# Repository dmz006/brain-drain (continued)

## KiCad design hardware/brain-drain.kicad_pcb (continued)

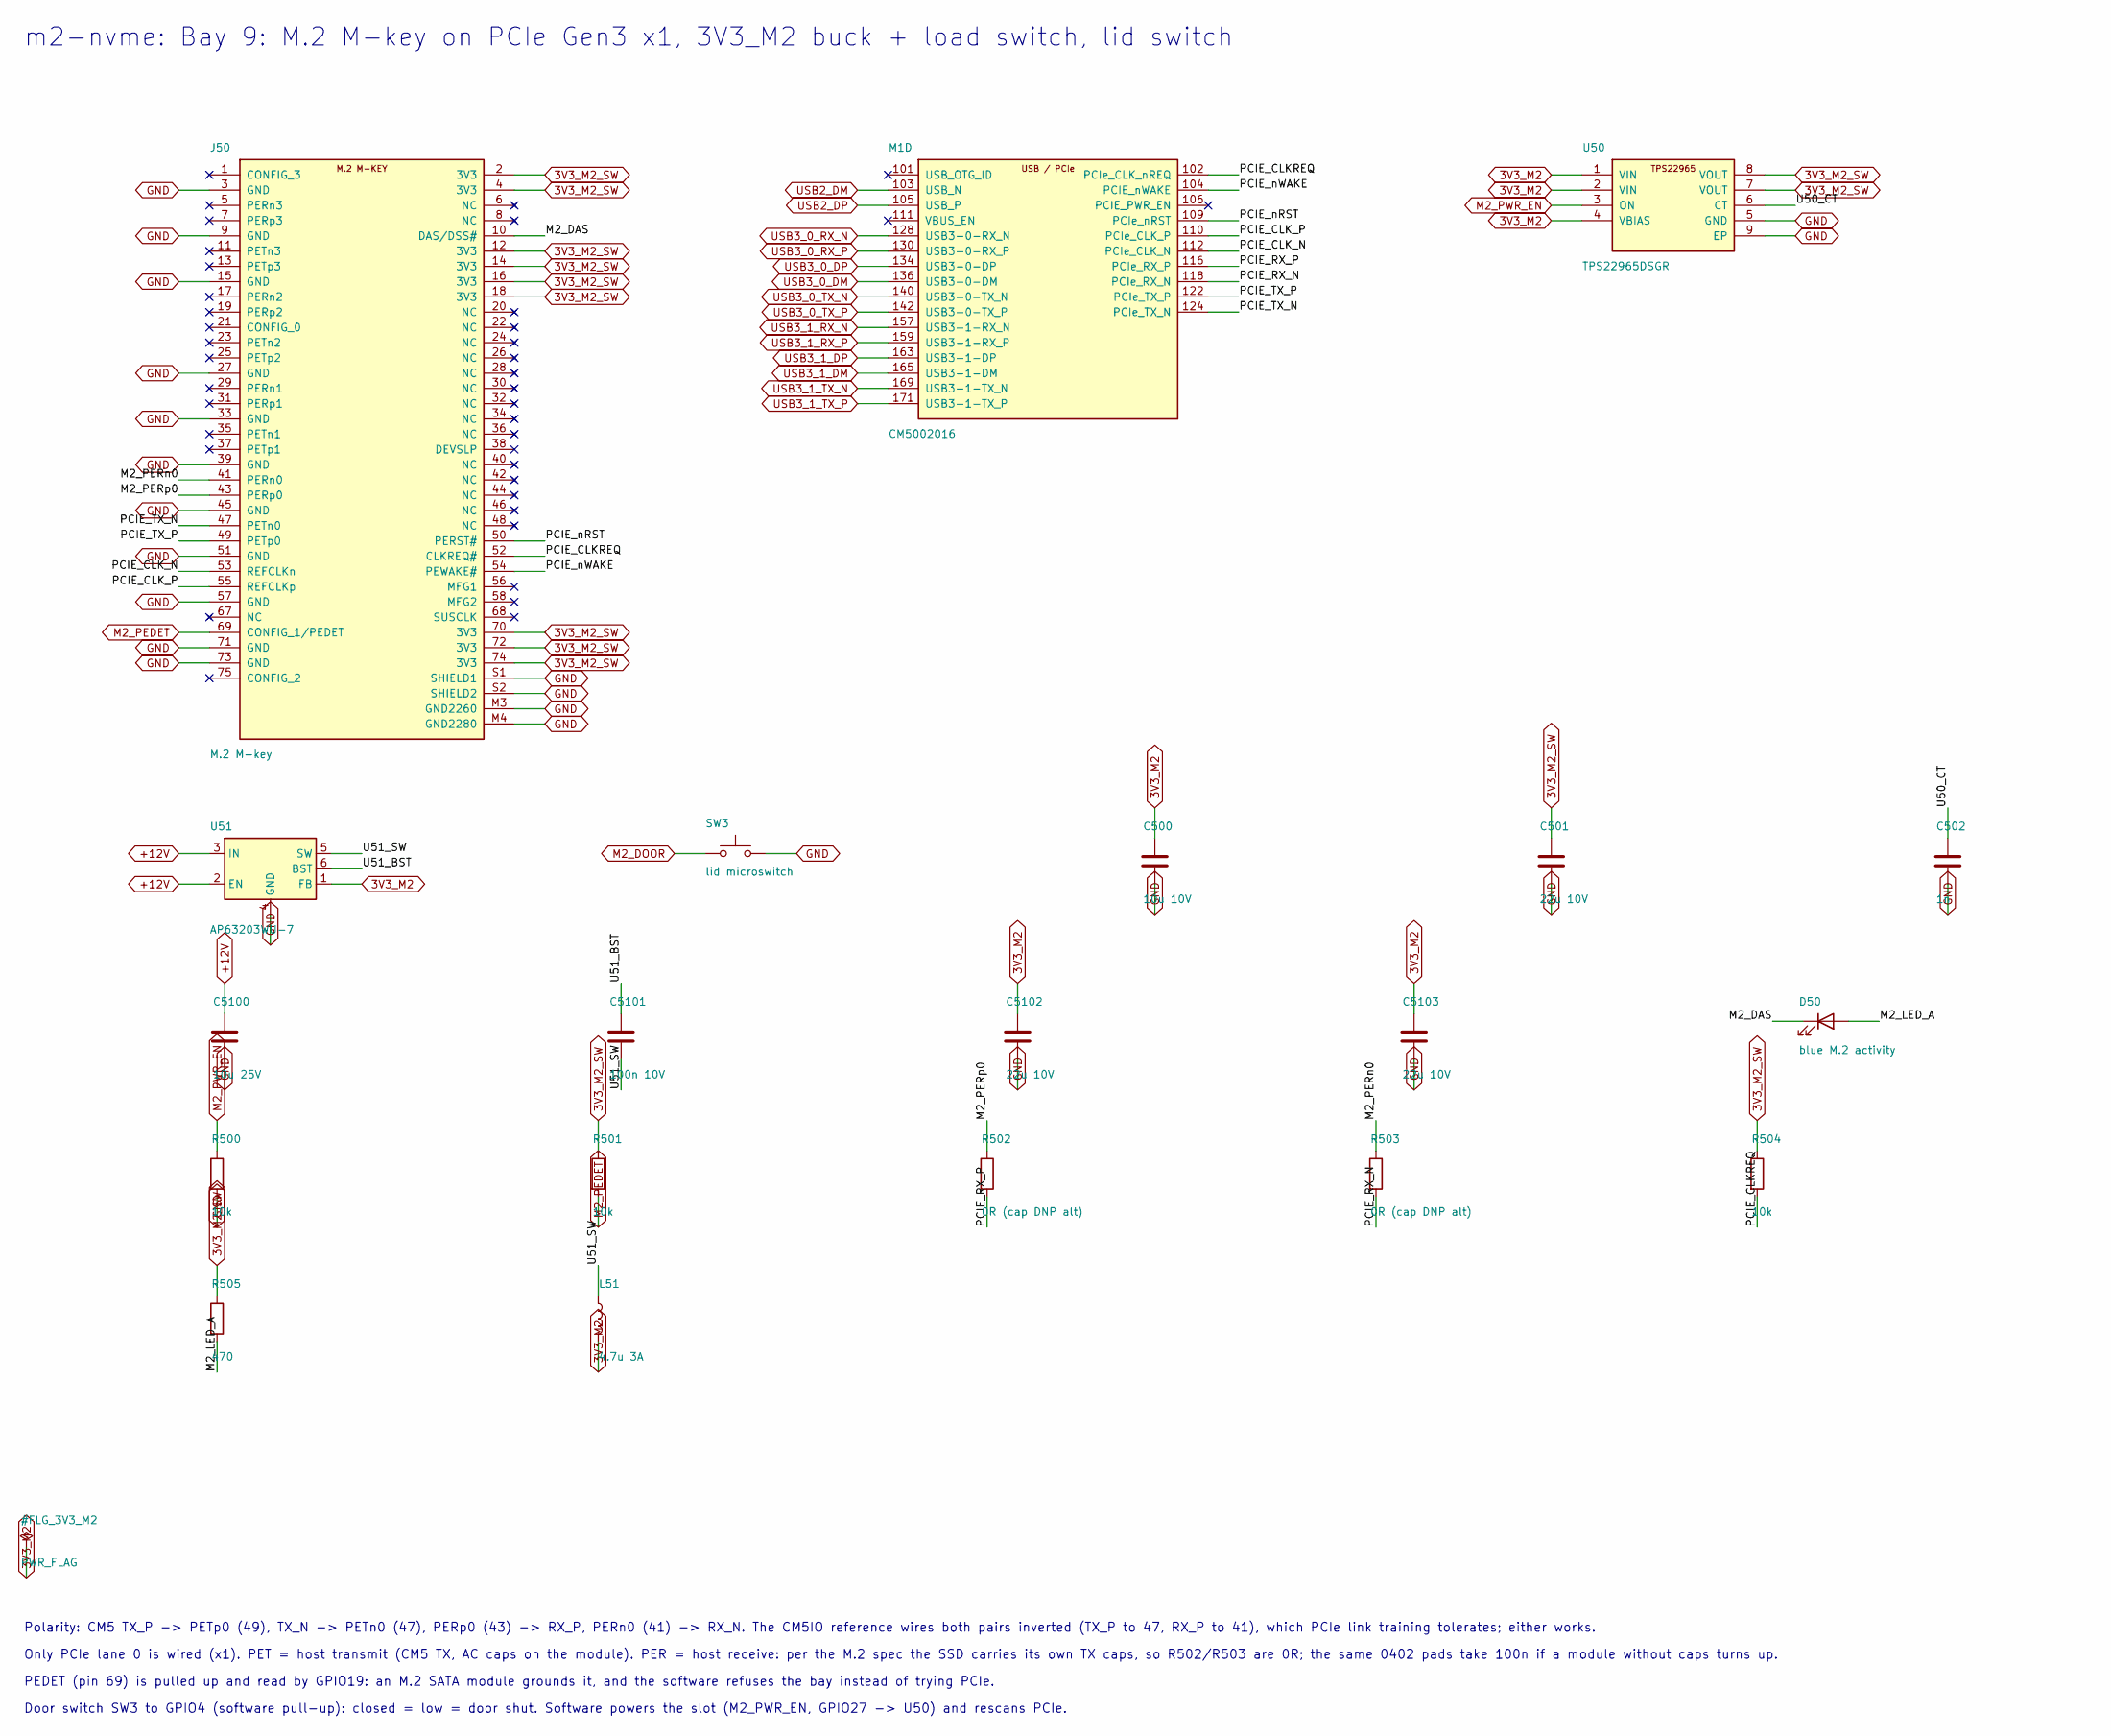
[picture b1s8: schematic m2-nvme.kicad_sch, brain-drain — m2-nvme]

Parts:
C500: 10u 10V; C_0805_2012Metric
C501, C5102, C5103: 22u 10V; C_0805_2012Metric
C502: 1n; C_0402_1005Metric
C5100: 10u 25V; C_1210_3225Metric
C5101: 100n 10V; C_0402_1005Metric
D50: blue M.2 activity; LED_D3.0mm
J50: M.2 M-key; M2_Socket3_MKey_CM5IO
L51: 4.7u 3A; L_Taiyo-Yuden_NR-40xx
M1: CM5002016; Raspberry-Pi-5-Compute-Module
R500, R501, R504: 10k; R_0402_1005Metric
R502, R503: 0R (cap DNP alt); C_0402_1005Metric
R505: 470; R_0402_1005Metric
SW3: lid microswitch; SW_PUSH_6mm
U50: TPS22965DSGR; Texas_DSG0008A_WSON-8-1EP_2x2mm_P0.5mm_EP0.9x1.6mm
U51: AP63203WU-7; TSOT-23-6

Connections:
3V3_M2: C500.1, C5102.1, C5103.1, L51.2, U50.1 (VIN), U50.2 (VIN), U50.4 (VBIAS), U51.1 (FB)
3V3_M2_SW: C501.1, J50.2 (3V3), J50.4 (3V3), J50.12 (3V3), J50.14 (3V3), J50.16 (3V3), J50.18 (3V3), J50.70 (3V3), J50.72 (3V3), J50.74 (3V3), R501.1, R504.1, R505.1, U50.7 (VOUT), U50.8 (VOUT)
+12V: C5100.1, U51.2 (EN), U51.3 (IN); also elsewhere on the board
GND: C500.2, C501.2, C502.2, C5100.2, C5102.2, C5103.2, J50.3 (GND), J50.9 (GND), J50.15 (GND), J50.27 (GND), J50.33 (GND), J50.39 (GND), J50.45 (GND), J50.51 (GND), J50.57 (GND), J50.71 (GND), J50.73 (GND), J50.M3 (GND2260), J50.M4 (GND2280), J50.S1 (SHIELD1), J50.S2 (SHIELD2), R500.2, SW3.2, U50.5 (GND), U50.9 (EP), U51.4 (GND); also elsewhere on the board
M2_DAS: D50.1 (K), J50.10 (DAS/DSS#)
M2_DOOR: SW3.1; also elsewhere on the board
M2_LED_A: D50.2 (A), R505.2
M2_PEDET: J50.69 (CONFIG_1/PEDET), R501.2; also elsewhere on the board
M2_PERn0: J50.41 (PERn0), R503.1
M2_PERp0: J50.43 (PERp0), R502.1
M2_PWR_EN: R500.1, U50.3 (ON); also elsewhere on the board
PCIE_CLKREQ: J50.52 (CLKREQ#), M1.102 (PCIe_CLK_nREQ), R504.2
PCIE_CLK_N: J50.53 (REFCLKn), M1.112 (PCIe_CLK_N)
PCIE_CLK_P: J50.55 (REFCLKp), M1.110 (PCIe_CLK_P)
PCIE_RX_N: M1.118 (PCIe_RX_N), R503.2
PCIE_RX_P: M1.116 (PCIe_RX_P), R502.2
PCIE_TX_N: J50.47 (PETn0), M1.124 (PCIe_TX_N)
PCIE_TX_P: J50.49 (PETp0), M1.122 (PCIe_TX_P)
PCIE_nRST: J50.50 (PERST#), M1.109 (PCIe_nRST)
PCIE_nWAKE: J50.54 (PEWAKE#), M1.104 (PCIE_nWAKE)
U50_CT: C502.1, U50.6 (CT)
U51_BST: C5101.1, U51.6 (BST)
U51_SW: C5101.2, L51.1, U51.5 (SW)
USB2_DM: M1.103 (USB_N); also elsewhere on the board
USB2_DP: M1.105 (USB_P); also elsewhere on the board
USB3_0_DM: M1.136 (USB3-0-DM); also elsewhere on the board
USB3_0_DP: M1.134 (USB3-0-DP); also elsewhere on the board
USB3_0_RX_N: M1.128 (USB3-0-RX_N); also elsewhere on the board
USB3_0_RX_P: M1.130 (USB3-0-RX_P); also elsewhere on the board
USB3_0_TX_N: M1.140 (USB3-0-TX_N); also elsewhere on the board
USB3_0_TX_P: M1.142 (USB3-0-TX_P); also elsewhere on the board
USB3_1_DM: M1.165 (USB3-1-DM); also elsewhere on the board
USB3_1_DP: M1.163 (USB3-1-DP); also elsewhere on the board
USB3_1_RX_N: M1.157 (USB3-1-RX_N); also elsewhere on the board
USB3_1_RX_P: M1.159 (USB3-1-RX_P); also elsewhere on the board
USB3_1_TX_N: M1.169 (USB3-1-TX_N); also elsewhere on the board
USB3_1_TX_P: M1.171 (USB3-1-TX_P); also elsewhere on the board

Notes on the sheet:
m2-nvme: Bay 9: M.2 M-key on PCIe Gen3 x1, 3V3_M2 buck + load switch, lid switch
Polarity: CM5 TX_P -> PETp0 (49), TX_N -> PETn0 (47), PERp0 (43) -> RX_P, PERn0 (41) -> RX_N. The CM5IO reference wires both pairs inverted (TX_P to 47, RX_P to 41), which PCIe link training tolerates; either works.
Only PCIe lane 0 is wired (x1). PET = host transmit (CM5 TX, AC caps on the module). PER = host receive: per the M.2 spec the SSD carries its own TX caps, so R502/R503 are 0R; the same 0402 pads take 100n if a module without caps turns up.
PEDET (pin 69) is pulled up and read by GPIO19: an M.2 SATA module grounds it, and the software refuses the bay instead of trying PCIe.
Door switch SW3 to GPIO4 (software pull-up): closed = low = door shut. Software powers the slot (M2_PWR_EN, GPIO27 -> U50) and rescans PCIe.

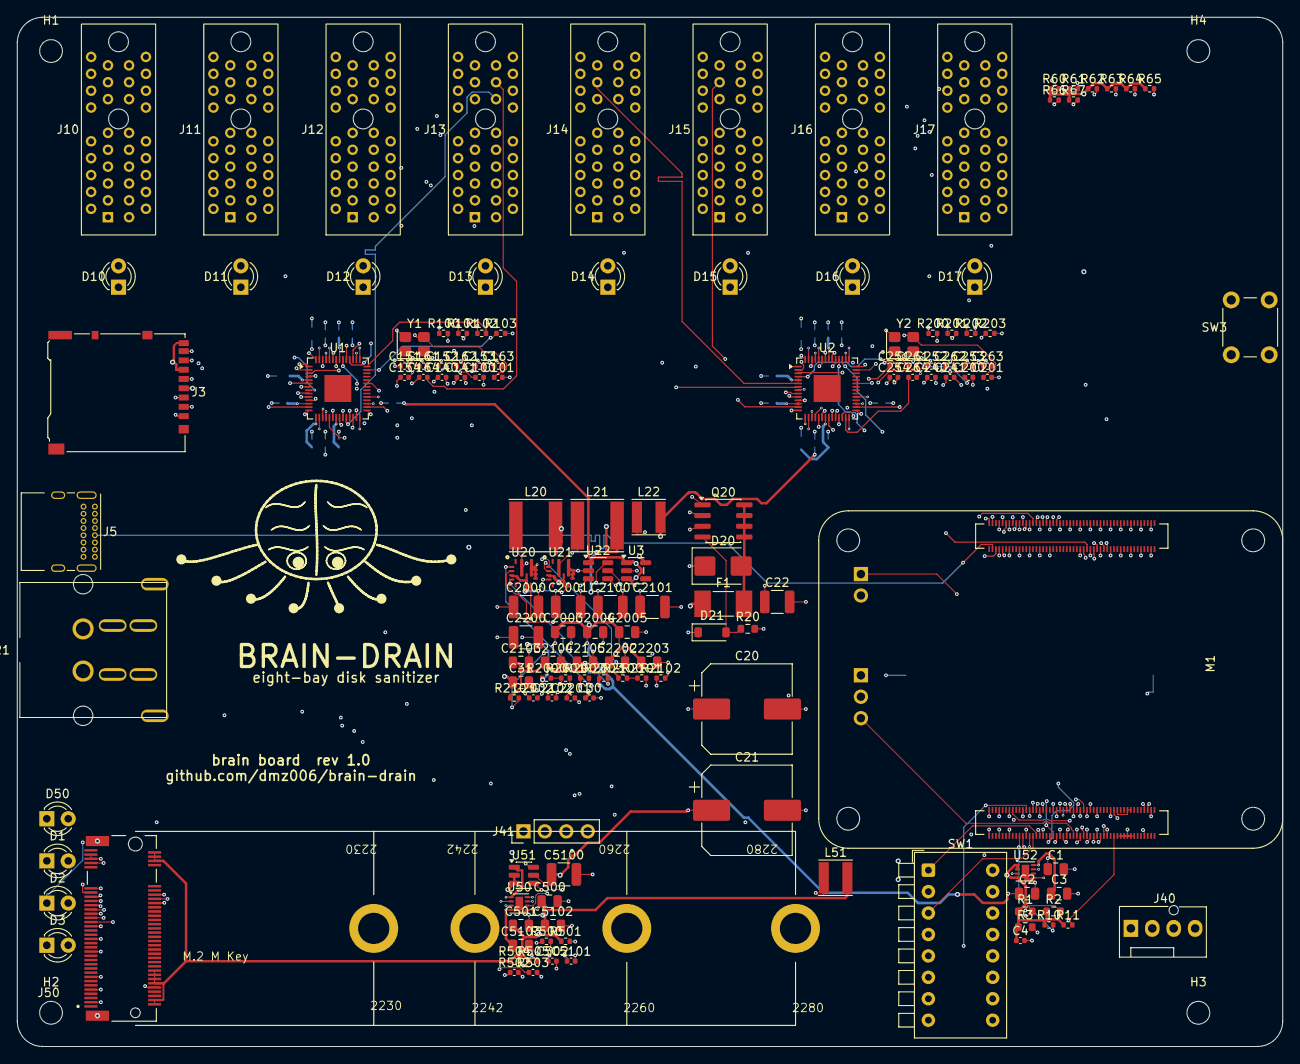
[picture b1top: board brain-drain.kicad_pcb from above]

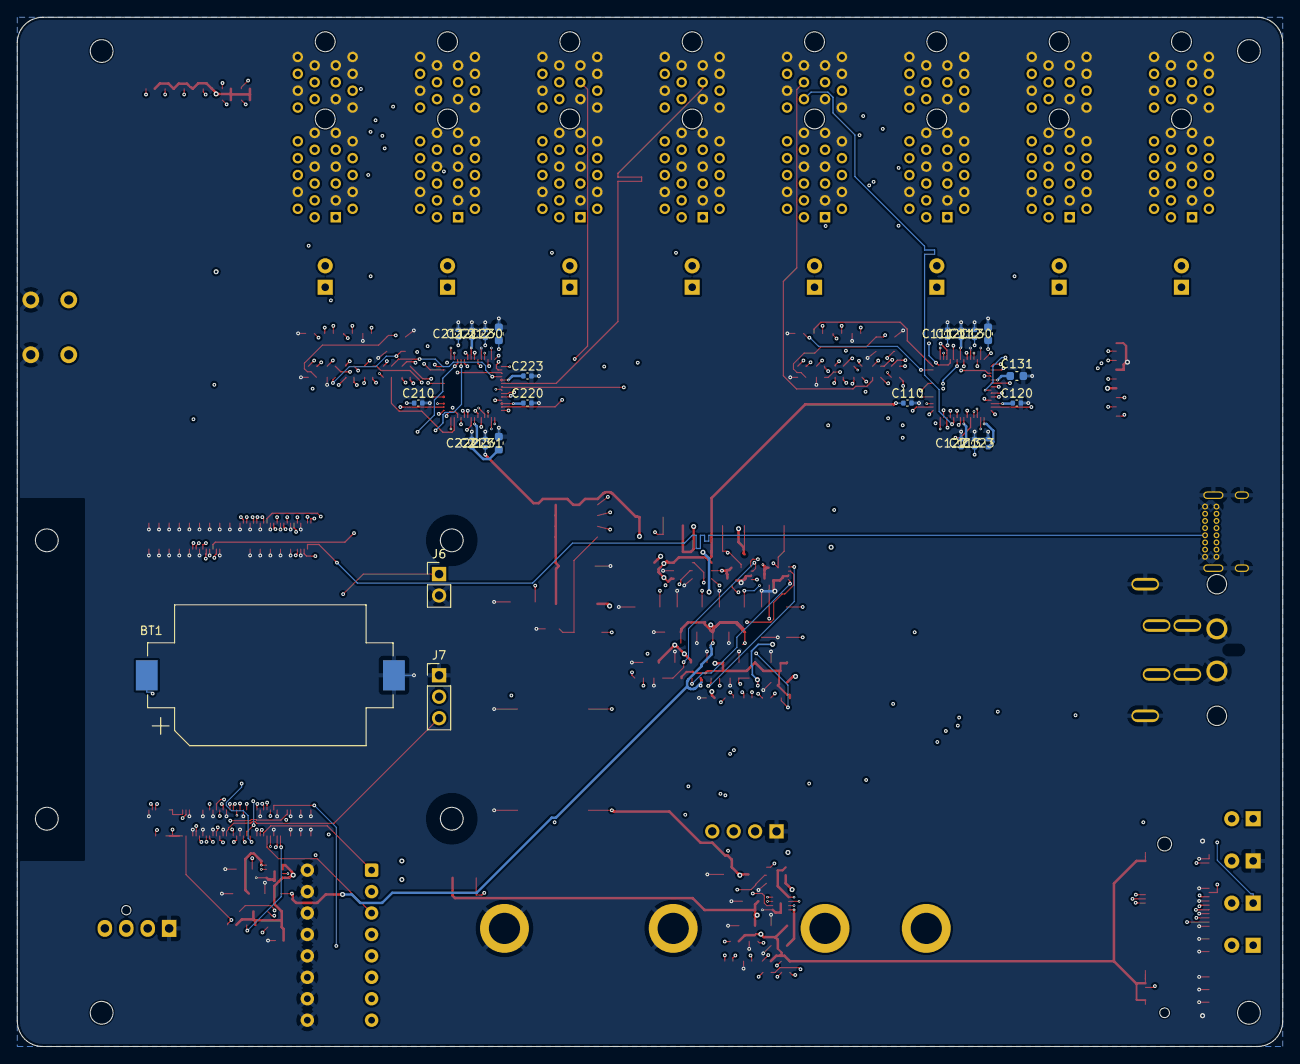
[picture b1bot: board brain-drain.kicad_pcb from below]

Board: 6 copper layers, 150.0 x 122.0 mm, 167 parts (23 on the bottom side), 192 nets.

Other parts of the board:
H1, H2, H3, H4: M2.5; MountingHole_2.7mm_M2.5

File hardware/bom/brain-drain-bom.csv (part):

refs,qty,value,footprint,manufacturer,mpn,description,usd_each,usd_total,status
BT1,1,CR2032,BatteryHolder_Keystone_1060_1x2032,Keystone,1060,"CR2032 SMD holder (cell bought separately, about 0.5)",0.9,0.9,verify
"C1,C2,C501,C2003,C2004,C2005,C2103,C2104,C2105,C2202,C2203,C5102,C5103",13,22u 10V,C_0805_2012Metric,generic,,22 uF X5R 10 V 0805,0.08,1.04,
"C3,C31,C500",3,10u 10V,C_0805_2012Metric,generic,,10 uF X5R 10 V 0805,0.05,0.15,
"C4,C30",2,1u 10V,C_0402_1005Metric,generic,,1 uF X5R 10 V 0402,0.02,0.04,
"C20,C21",2,680u 25V low-ESR,CP_Elec_10x10.5,generic,,"680 uF 25 V low-ESR aluminium polymer or electrolytic, 10 x 10.5 mm SMD (spin-up bulk)",0.9,1.8,verify
"C22,C2000,C2001,C2100,C2101,C2200,C5100",7,10u 25V,C_1210_3225Metric,generic,,10 uF X5R 25 V 1210 (input and 5 V bulk),0.12,0.84,
"C100,C101,C200,C201",4,33p,C_0402_1005Metric,generic,,33 pF C0G 50 V 0402 (crystal load),0.01,0.04,
"C110,C111,C112,C113,C120,C121,C122,C123,C140,C141,C151,C152,C153,C154,C161,C162,C163,C164,C210,C211,C212,C213,C220,C221,C222,C223,C240,C241,C251,C252,C253,C254,C261,C262,C263,C264",36,100n,C_0402_1005Metric,generic,,"100 nF X7R 16 V or better, 0402",0.01,0.36,
"C130,C131,C230,C231",4,4.7u 10V,C_0603_1608Metric,generic,,4.7 uF X5R 10 V 0603,0.04,0.16,
C502,1,1n,C_0402_1005Metric,generic,,1 nF C0G 50 V 0402,0.01,0.01,
"C2002,C2102",2,100n 25V,C_0402_1005Metric,generic,,"100 nF X7R 16 V or better, 0402",0.01,0.02,
"C2201,C5101",2,100n 10V,C_0402_1005Metric,generic,,"100 nF X7R 16 V or better, 0402",0.01,0.02,
D1,1,green PWR,LED_D3.0mm,generic,,"3 mm through-hole LED, colour as listed, 2 V forward, about 5 mA",0.1,0.1,
D2,1,green ACT,LED_D3.0mm,generic,,"3 mm through-hole LED, colour as listed, 2 V forward, about 5 mA",0.1,0.1,
D3,1,red STATUS,LED_D3.0mm,generic,,"3 mm through-hole LED, colour as listed, 2 V forward, about 5 mA",0.1,0.1,
D10,1,blue bay 1 activity,LED_D3.0mm,generic,,"3 mm through-hole LED, colour as listed, 2 V forward, about 5 mA",0.1,0.1,
D11,1,blue bay 2 activity,LED_D3.0mm,generic,,"3 mm through-hole LED, colour as listed, 2 V forward, about 5 mA",0.1,0.1,
D12,1,blue bay 3 activity,LED_D3.0mm,generic,,"3 mm through-hole LED, colour as listed, 2 V forward, about 5 mA",0.1,0.1,
D13,1,blue bay 4 activity,LED_D3.0mm,generic,,"3 mm through-hole LED, colour as listed, 2 V forward, about 5 mA",0.1,0.1,
D14,1,blue bay 5 activity,LED_D3.0mm,generic,,"3 mm through-hole LED, colour as listed, 2 V forward, about 5 mA",0.1,0.1,
D15,1,blue bay 6 activity,LED_D3.0mm,generic,,"3 mm through-hole LED, colour as listed, 2 V forward, about 5 mA",0.1,0.1,
D16,1,blue bay 7 activity,LED_D3.0mm,generic,,"3 mm through-hole LED, colour as listed, 2 V forward, about 5 mA",0.1,0.1,
D17,1,blue bay 8 activity,LED_D3.0mm,generic,,"3 mm through-hole LED, colour as listed, 2 V forward, about 5 mA",0.1,0.1,
D20,1,SMBJ15A,D_SMB,Littelfuse,SMBJ15A,"TVS diode 15 V standoff, SMB",0.35,0.35,
D21,1,12V 0.5W,D_SOD-123,generic,,"12 V 0.5 W zener, SOD-123 (BZT52C12 class)",0.05,0.05,
D50,1,blue M.2 activity,LED_D3.0mm,generic,,"3 mm through-hole LED, colour as listed, 2 V forward, about 5 mA",0.1,0.1,
F1,1,15A slow 0453015.MR,Fuse_Littelfuse-NANO2-451_453,Littelfuse,0453015.MR,NANO2 15 A slow-blow fuse (C31; check the 15 A rating in stock),0.8,0.8,verify
J3,1,microSD,microSD_HC_Hirose_DM3AT-SF-PEJM5,Hirose,DM3AT-SF-PEJM5,microSD push-push socket,1.0,1.0,verify
J5,1,USB-C rpiboot,USB_C_Receptacle_GCT_USB4085,GCT,USB4085-GF-A,"USB-C 16-pin receptacle, USB 2.0 only",1.0,1.0,
J6,1,nRPIBOOT,PinHeader_1x02_P2.54mm_Vertical,generic,,"2.54 mm pin header, vertical, count as listed",0.1,0.1,
J7,1,UART0 GND/TX/RX,PinHeader_1x03_P2.54mm_Vertical,generic,,"2.54 mm pin header, vertical, count as listed",0.1,0.1,
J10,1,bay slot 1,PCIe_x1_Socket_THT,Amphenol FCI,10018783-10100TLF,"PCI Express x1 vertical through-hole socket, 36 contacts (custom bay pinout, no PCIe signalling)",1.0,1.0,verify
J11,1,bay slot 2,PCIe_x1_Socket_THT,Amphenol FCI,10018783-10100TLF,"PCI Express x1 vertical through-hole socket, 36 contacts (custom bay pinout, no PCIe signalling)",1.0,1.0,verify
J12,1,bay slot 3,PCIe_x1_Socket_THT,Amphenol FCI,10018783-10100TLF,"PCI Express x1 vertical through-hole socket, 36 contacts (custom bay pinout, no PCIe signalling)",1.0,1.0,verify
J13,1,bay slot 4,PCIe_x1_Socket_THT,Amphenol FCI,10018783-10100TLF,"PCI Express x1 vertical through-hole socket, 36 contacts (custom bay pinout, no PCIe signalling)",1.0,1.0,verify
J14,1,bay slot 5,PCIe_x1_Socket_THT,Amphenol FCI,10018783-10100TLF,"PCI Express x1 vertical through-hole socket, 36 contacts (custom bay pinout, no PCIe signalling)",1.0,1.0,verify
J15,1,bay slot 6,PCIe_x1_Socket_THT,Amphenol FCI,10018783-10100TLF,"PCI Express x1 vertical through-hole socket, 36 contacts (custom bay pinout, no PCIe signalling)",1.0,1.0,verify
J16,1,bay slot 7,PCIe_x1_Socket_THT,Amphenol FCI,10018783-10100TLF,"PCI Express x1 vertical through-hole socket, 36 contacts (custom bay pinout, no PCIe signalling)",1.0,1.0,verify
J17,1,bay slot 8,PCIe_x1_Socket_THT,Amphenol FCI,10018783-10100TLF,"PCI Express x1 vertical through-hole socket, 36 contacts (custom bay pinout, no PCIe signalling)",1.0,1.0,verify
J21,1,KPJX-4S-S,Kycon_KPJX-4S-S,Kycon,KPJX-4S-S,"4-pin mini-DIN power jack, shielded, 7.5 A per pin",1.5,1.5,
J40,1,Fan GND/5V/TACH/PWM,FanPinHeader_1x04_P2.54mm_Vertical,generic,,"2.54 mm pin header, vertical, count as listed",0.1,0.1,
J41,1,OLED GND/VCC/SCL/SDA,PinHeader_1x04_P2.54mm_Vertical,generic,,"2.54 mm pin header, vertical, count as listed",0.1,0.1,
J50,1,M.2 M-key,M2_Socket3_MKey_CM5IO,TE Connectivity,2199230-4,"M.2 M-key socket, 4.2 mm, for a 2280 module",1.2,1.2,
"L20,L21",2,2.2u 8A,L_Taiyo-Yuden_NR-60xx,generic,,"2.2 uH, 8 A saturation, shielded, 6 x 6 mm (TPS56637 reference design class)",0.6,1.2,verify
"L22,L51",2,4.7u 3A,L_Taiyo-Yuden_NR-40xx,generic,,"4.7 uH, 3 A, shielded, 4 x 4 mm (AP63203 class)",0.35,0.7,verify
M1,1,CM5002016,Raspberry-Pi-5-Compute-Module,Raspberry Pi,CM5102016,"Compute Module 5, wireless, 2 GB RAM, 16 GB eMMC (the schematic value field still reads CM5002016)",97.0,97.0,verify
Q20,1,AO4407A,SOIC-8_3.9x4.9mm_P1.27mm,Alpha & Omega,AO4407A,"P-MOSFET -30 V, SO-8: S 1-3, G 4, D 5-8 (reverse-polarity protection)",0.8,0.8,
"R1,R2,R3",3,1k,R_0603_1608Metric,generic,,"resistor 1 %, thick film (value as listed)",0.005,0.015,
"R10,R11,R101,R102,R201,R202,R500,R501,R504,R2001,R2003,R2101,R2103",13,10k,R_0402_1005Metric,generic,,"resistor 1 %, thick film (value as listed)",0.005,0.065,
R20,1,100k,R_0603_1608Metric,generic,,"resistor 1 %, thick film (value as listed)",0.005,0.005,
"R60,R61,R62,R63,R64,R65,R66,R67,R505",9,470,R_0402_1005Metric,generic,,"resistor 1 %, thick film (value as listed)",0.005,0.045,
"R100,R200",2,12.0k 1%,R_0402_1005Metric,generic,,"resistor 1 %, thick film (value as listed)",0.005,0.01,
"R103,R203",2,200k,R_0402_1005Metric,generic,,"resistor 1 %, thick film (value as listed)",0.005,0.01,
"R502,R503",2,0R (cap DNP alt),C_0402_1005Metric,generic,,"0 ohm 0402 (option link, cap DNP alternative)",0.005,0.01,
"R2000,R2100",2,73.2k,R_0402_1005Metric,generic,,"resistor 1 %, thick film (value as listed)",0.005,0.01,
"R2002,R2102",2,100k,R_0402_1005Metric,generic,,"resistor 1 %, thick film (value as listed)",0.005,0.01,
SW1,1,DIP x8,SW_DIP_SPSTx08_Piano_10.8x21.88mm_W7.62mm_P2.54mm,generic,,"8-position piano DIP switch, 2.54 mm pitch, 7.62 mm row",1.0,1.0,verify
SW3,1,lid microswitch,SW_PUSH_6mm,generic,,6 mm tactile switch used as the lid switch,0.2,0.2,
"U1,U2",2,USB5744/2G,QFN-56-1EP_7x7mm_P0.4mm_EP3.2x3.2mm,Microchip,USB5744/2G,"USB 3.2 Gen 1 four-port hub, VQFN-56 7 x 7",2.44,4.88,
U3,1,AP2112K-1.2,SOT-23-5,Diodes Inc.,AP2112K-1.2TRG1,"600 mA LDO, 1.2 V, SOT-25 (hub core)",0.3,0.3,
"U20,U21",2,TPS56637RPAR,Texas_RPA0010A_VQFN-HR-10_3x3mm,Texas Instruments,TPS56637RPAR,"6 A step-down converter, VQFN-HR 3 x 3",1.9,3.8,
"U22,U51",2,AP63203WU-7,TSOT-23-6,Diodes Inc.,AP63203WU-7,"2 A step-down converter, TSOT-26, 3.3 V",0.5,1.0,
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
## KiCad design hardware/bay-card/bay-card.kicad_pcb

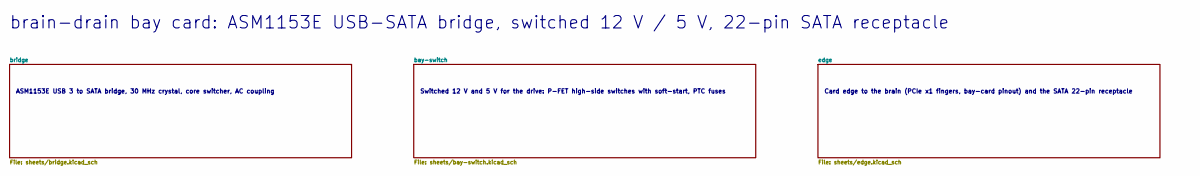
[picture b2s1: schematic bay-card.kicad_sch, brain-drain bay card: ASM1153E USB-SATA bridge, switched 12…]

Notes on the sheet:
brain-drain bay card: ASM1153E USB-SATA bridge, switched 12 V / 5 V, 22-pin SATA receptacle
ASM1153E USB 3 to SATA bridge, 30 MHz crystal, core switcher, AC coupling
Switched 12 V and 5 V for the drive: P-FET high-side switches with soft-start, PTC fuses
Card edge to the brain (PCIe x1 fingers, bay-card pinout) and the SATA 22-pin receptacle

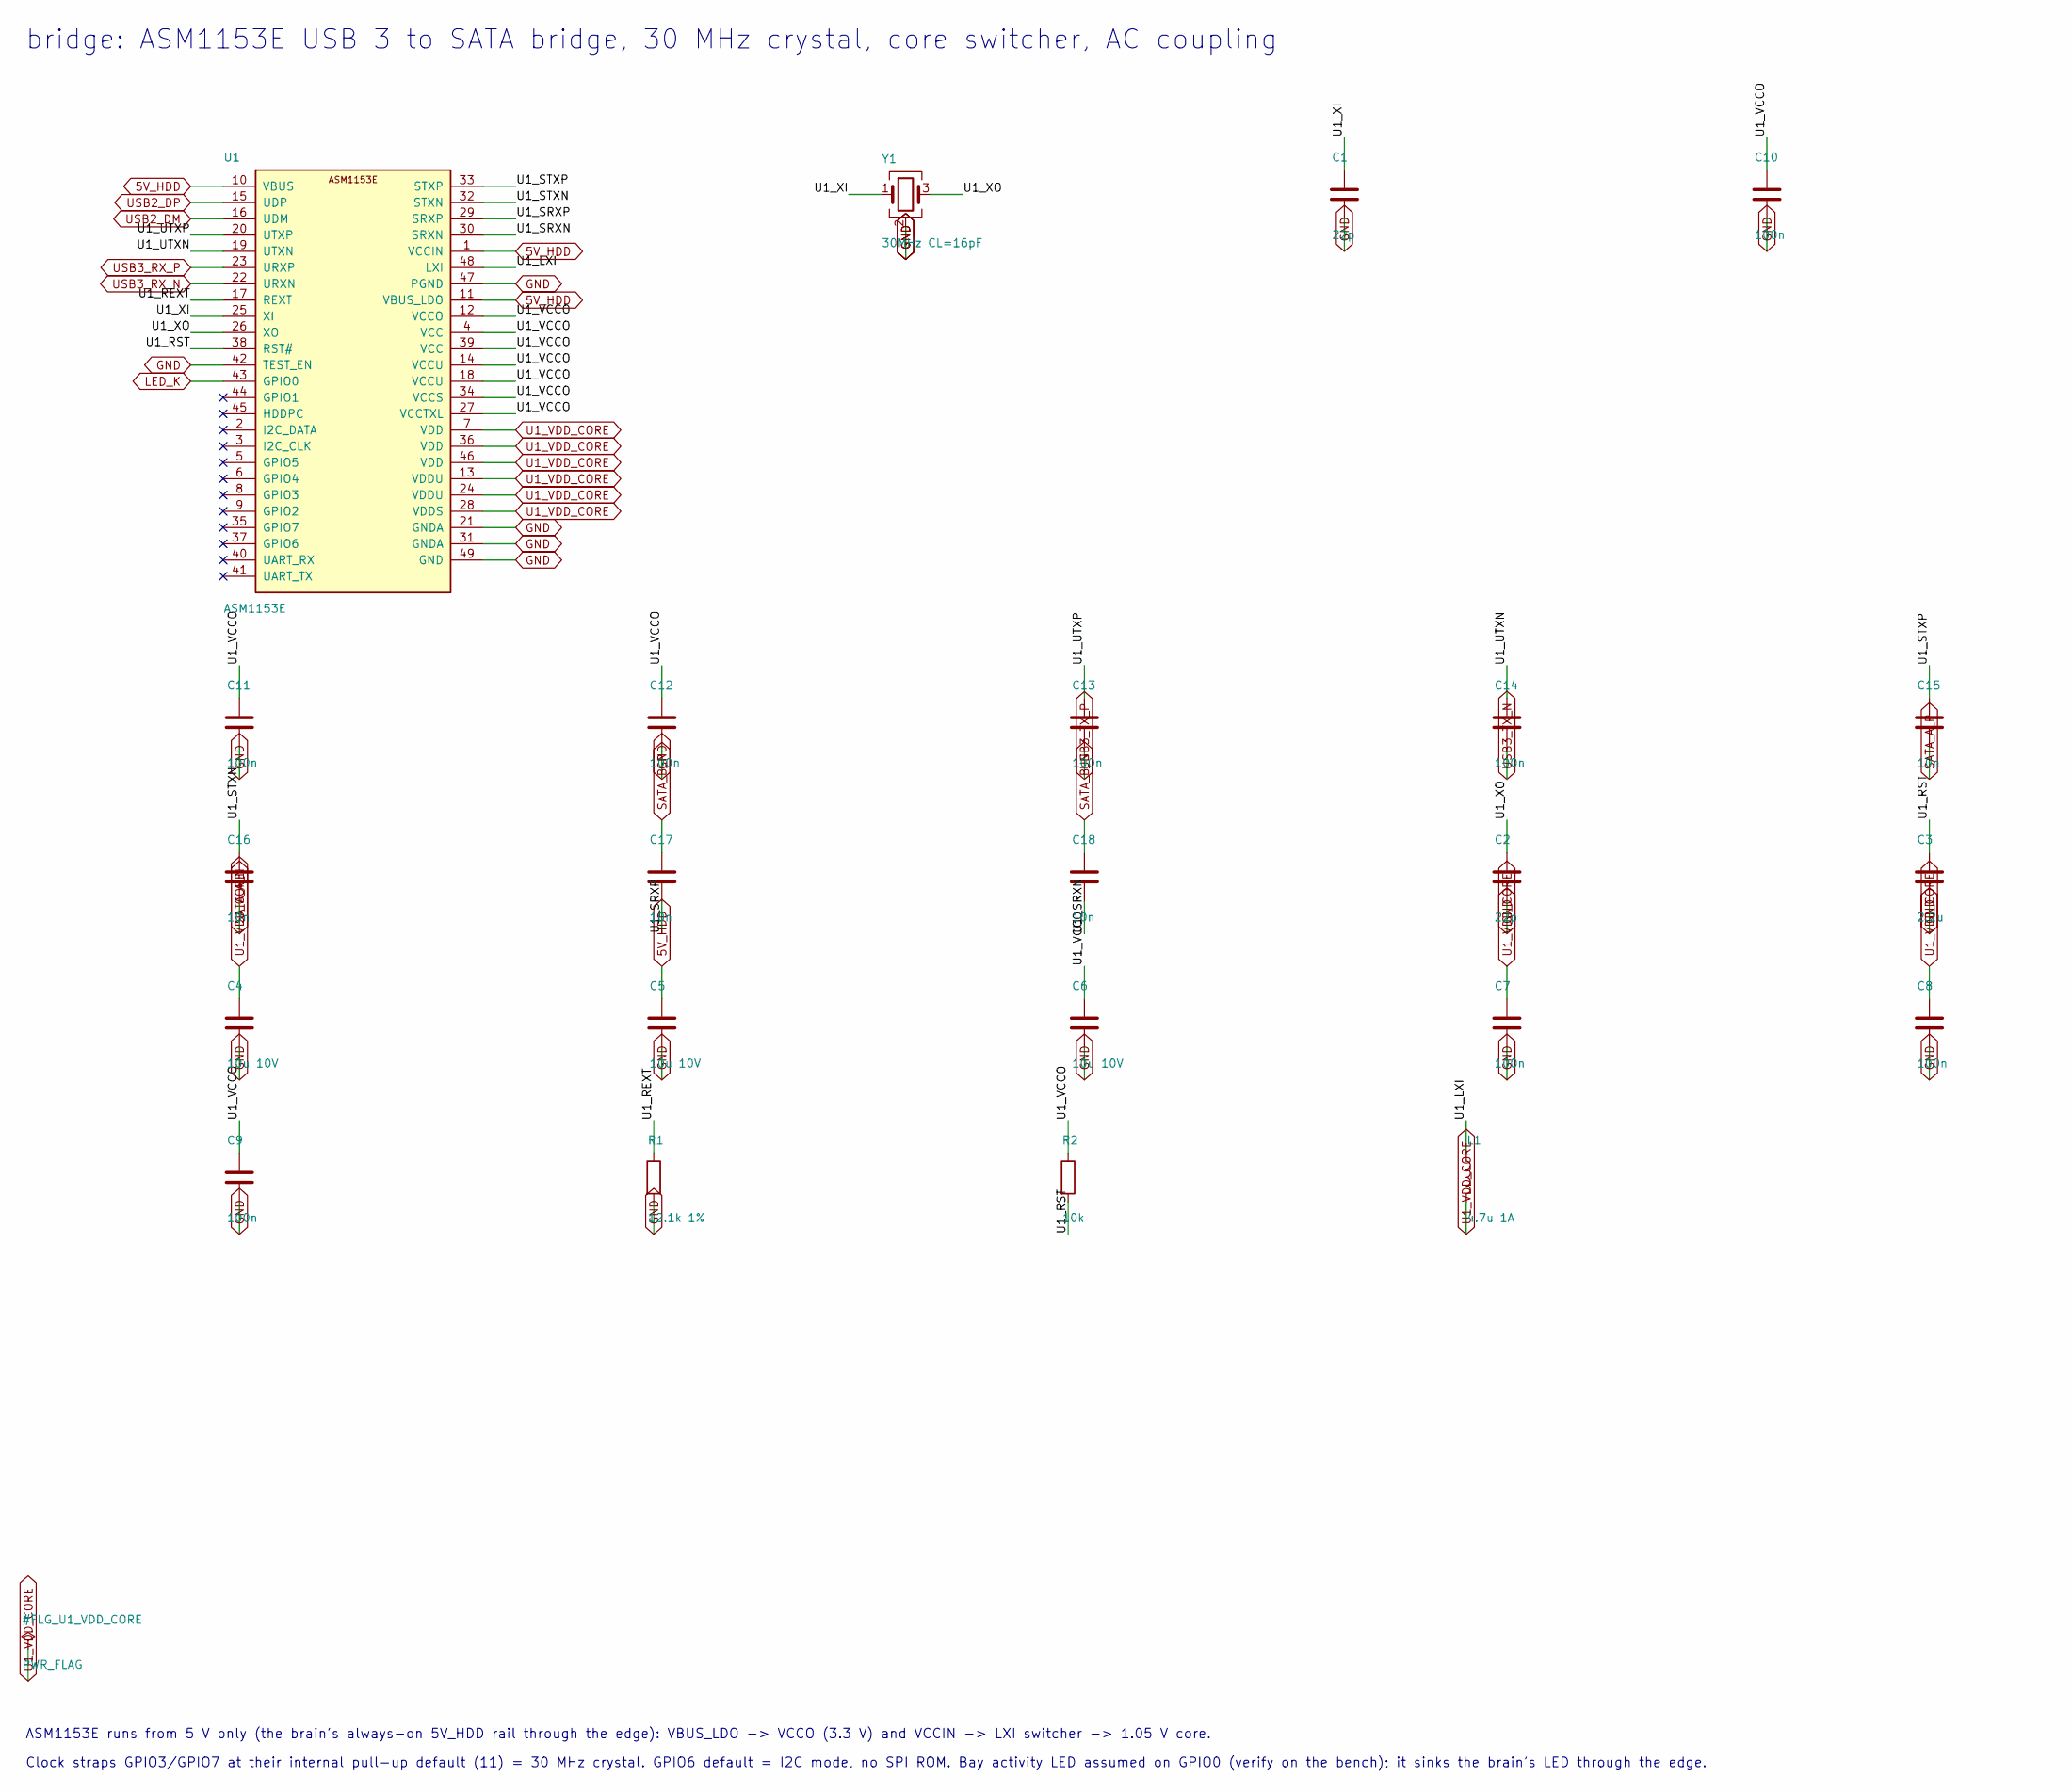
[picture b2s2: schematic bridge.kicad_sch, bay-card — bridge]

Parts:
C1, C2: 22p; C_0402_1005Metric
C3: 2.2u; C_0603_1608Metric
C4, C5, C6: 10u 10V; C_0805_2012Metric
C7, C8, C9, C10, C11, C12, C13, C14: 100n; C_0402_1005Metric
C15, C16, C17, C18: 10n; C_0402_1005Metric
L1: 4.7u 1A; L_Taiyo-Yuden_NR-40xx
R1: 12.1k 1%; R_0402_1005Metric
R2: 10k; R_0402_1005Metric
U1: ASM1153E; QFN-48-1EP_6x6mm_P0.4mm_EP4.6x4.6mm
Y1: 30MHz CL=16pF; Crystal_SMD_3225-4Pin_3.2x2.5mm

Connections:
5V_HDD: C5.1, U1.1 (VCCIN), U1.10 (VBUS), U1.11 (VBUS_LDO); also elsewhere on the board
GND: C1.2, C2.2, C3.2, C4.2, C5.2, C6.2, C7.2, C8.2, C9.2, C10.2, C11.2, C12.2, R1.2, U1.21 (GNDA), U1.31 (GNDA), U1.42 (TEST_EN), U1.47 (PGND), U1.49 (GND), Y1.2 (G), Y1.4 (G); also elsewhere on the board
LED_K: U1.43 (GPIO0); also elsewhere on the board
SATA_A_N: C16.2; also elsewhere on the board
SATA_A_P: C15.2; also elsewhere on the board
SATA_B_N: C18.1; also elsewhere on the board
SATA_B_P: C17.1; also elsewhere on the board
U1_LXI: L1.1, U1.48 (LXI)
U1_REXT: R1.1, U1.17 (REXT)
U1_RST: C3.1, R2.2, U1.38 (RST#)
U1_SRXN: C18.2, U1.30 (SRXN)
U1_SRXP: C17.2, U1.29 (SRXP)
U1_STXN: C16.1, U1.32 (STXN)
U1_STXP: C15.1, U1.33 (STXP)
U1_UTXN: C14.1, U1.19 (UTXN)
U1_UTXP: C13.1, U1.20 (UTXP)
U1_VCCO: C6.1, C9.1, C10.1, C11.1, C12.1, R2.1, U1.4 (VCC), U1.12 (VCCO), U1.14 (VCCU), U1.18 (VCCU), U1.27 (VCCTXL), U1.34 (VCCS), U1.39 (VCC)
U1_VDD_CORE: C4.1, C7.1, C8.1, L1.2, U1.7 (VDD), U1.13 (VDDU), U1.24 (VDDU), U1.28 (VDDS), U1.36 (VDD), U1.46 (VDD)
U1_XI: C1.1, U1.25 (XI), Y1.1
U1_XO: C2.1, U1.26 (XO), Y1.3
USB2_DM: U1.16 (UDM); also elsewhere on the board
USB2_DP: U1.15 (UDP); also elsewhere on the board
USB3_RX_N: U1.22 (URXN); also elsewhere on the board
USB3_RX_P: U1.23 (URXP); also elsewhere on the board
USB3_TX_N: C14.2; also elsewhere on the board
USB3_TX_P: C13.2; also elsewhere on the board

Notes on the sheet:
bridge: ASM1153E USB 3 to SATA bridge, 30 MHz crystal, core switcher, AC coupling
ASM1153E runs from 5 V only (the brain's always-on 5V_HDD rail through the edge): VBUS_LDO -> VCCO (3.3 V) and VCCIN -> LXI switcher -> 1.05 V core.
Clock straps GPIO3/GPIO7 at their internal pull-up default (11) = 30 MHz crystal. GPIO6 default = I2C mode, no SPI ROM. Bay activity LED assumed on GPIO0 (verify on the bench); it sinks the brain's LED through the edge.
